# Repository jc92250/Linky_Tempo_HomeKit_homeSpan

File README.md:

# Linky_Tempo_HomeKit

## Introduction

Ceci est la "V2" du projet Linky_Tempo:
L'objectif est de pouvoir accéder au status du délestage ainsi qu'à la possibilité d'annuler ce délestage depuis Internet.

## Le contexte

Le logement est en tout électrique.
Le contrat EDF est en offre Tempo.
En général, hors télétravail, l'appartement est vide dans la journée.
L'environnement informatique est orienté Apple (mac, iPhone, appleTV)

## Rappel du besoin

Le besoin est de délester le chauffage (le basculer en hors-gel) automatiquement:
- en heure pleine jour rouge (HPJR) et jour blanc (HPJW)
- en cas de surconsommation

A la demande, il faut pouvoir annuler le délestage en HPJW (mais pas en HPJR)
Cette annulation du délestage doit pouvoir se faire même si on se trouve hors de la maison.
 
## L'approche suivie

Par rapport au projet Linky_Tempo, l'approche suivie sera de:
- remplacer l'Arduino par un ESP32
- installer HomeSpan sur l'ESP32 pour qu'il soit vu comme un device HomeKit
- le configurer comme un "Thermostat"

Pourquoi "Thermostat" ?  
Car cela semble être le device dont les fonctionnalités sont les plus proches de celles qu'on veut obtenir.  
Voici ses différents modes de fonctionnement (CurrentHeatingCoolingState) et leur usage prévu:
- IDLE: utilisé, délestage possible en fonction des infos du Linky
- HEATING: délestage annulé, chauffage actif
- COOLING: pas utilisé

Concernant la commande (TargetHeatingCoolingState) on a:
- OFF: pas utilisé
- HEAT: annulation du délestage, activer le chauffage (sauf si surconsommation)
- COOL: pas utilisé
- AUTO: mode automatique (délestage HPJR, HPJW et surconsommation)

Le circuit a également un bouton poussoir permettant de basculer entre le mode automatique et le mode annulation du délestage.

Note: "Heater-Cooler" aurait peut-être pu être utilisé à la place de "Thermostat". Mais cette possibilité n'a pas été étudiée.

## Partie électronique
Le mode "Thermostat" de HomeKit permettant d'afficher une température, une sonde BME280 a été rajoutée au projet.
Le circuit a été monté sur une plaque à trous avec bandes cuivrées. Dans KiCad, la couche "bleue" (B\.cu) corresponds à la face cuivrée alors que la couche "rouge" (F\.Cu) corresponds à la face supérieure sur laquelle on a installé quelques jumpers.
La disposition des composants est très aérée afin de limiter les court-circuits.

## Configuration

Factory reset:  
Faire un appui long (> 10 secondes) sur le bouton reset. Au bout de 3 secondes, la led interne va clignoter rapidement, continuer l'appui sur le bouton jusqu'à l'extinction de la led.

A ce moment, le device est configuré comme un point d'accès wifi sur lequel on peut se connecter avec un ordinateur ou un smartphone. Voici les paramètres du point d'accès:
- nom du wifi: JCDELESTAGE
- mot de passe: 123456789

Via ce point d'accès, il est possible de:
- définir le réseau wifi sur lequel le device doit se connecter
- définir le setup-code homeKit du device

Une fois ces informations saisies, le device va redémarrer et se connecter à ce
réseau wifi. Une fois ceci effectué, la led bleue va flasher 2 fois toutes les 3 secondes pour indiquer qu'il n'est pas encore pairé dans Maison.

## Les LEDs

LED rouge:
- toujours allumée, indique que l'ESP32 est alimenté

LED bleue:  
- allumée fixe: le device est en fonctionnement et pairé dans Maison
- allumée et clignotante (2 flashs brefs toutes les 3 secondes): le device n'est pas pairé dans Maison.

LED jaune:
- flashe à chaque fois qu'une trame Linky valide a été reçue
- reste allumée lorsque le délestage est annulé

## Limitation

A l'allumage du circuit, le chauffage est initilisé en mode délestage.
Il n'est pas possible de désactiver ce délestage et commencer à chauffer.
Il faut attendre quelques (4, cf TEMPS_DELESTAGE) minutes.

## Quelques informations techniques

Utiliser Arduino IDE pour builder le code et l'uploader sur l'ESP32

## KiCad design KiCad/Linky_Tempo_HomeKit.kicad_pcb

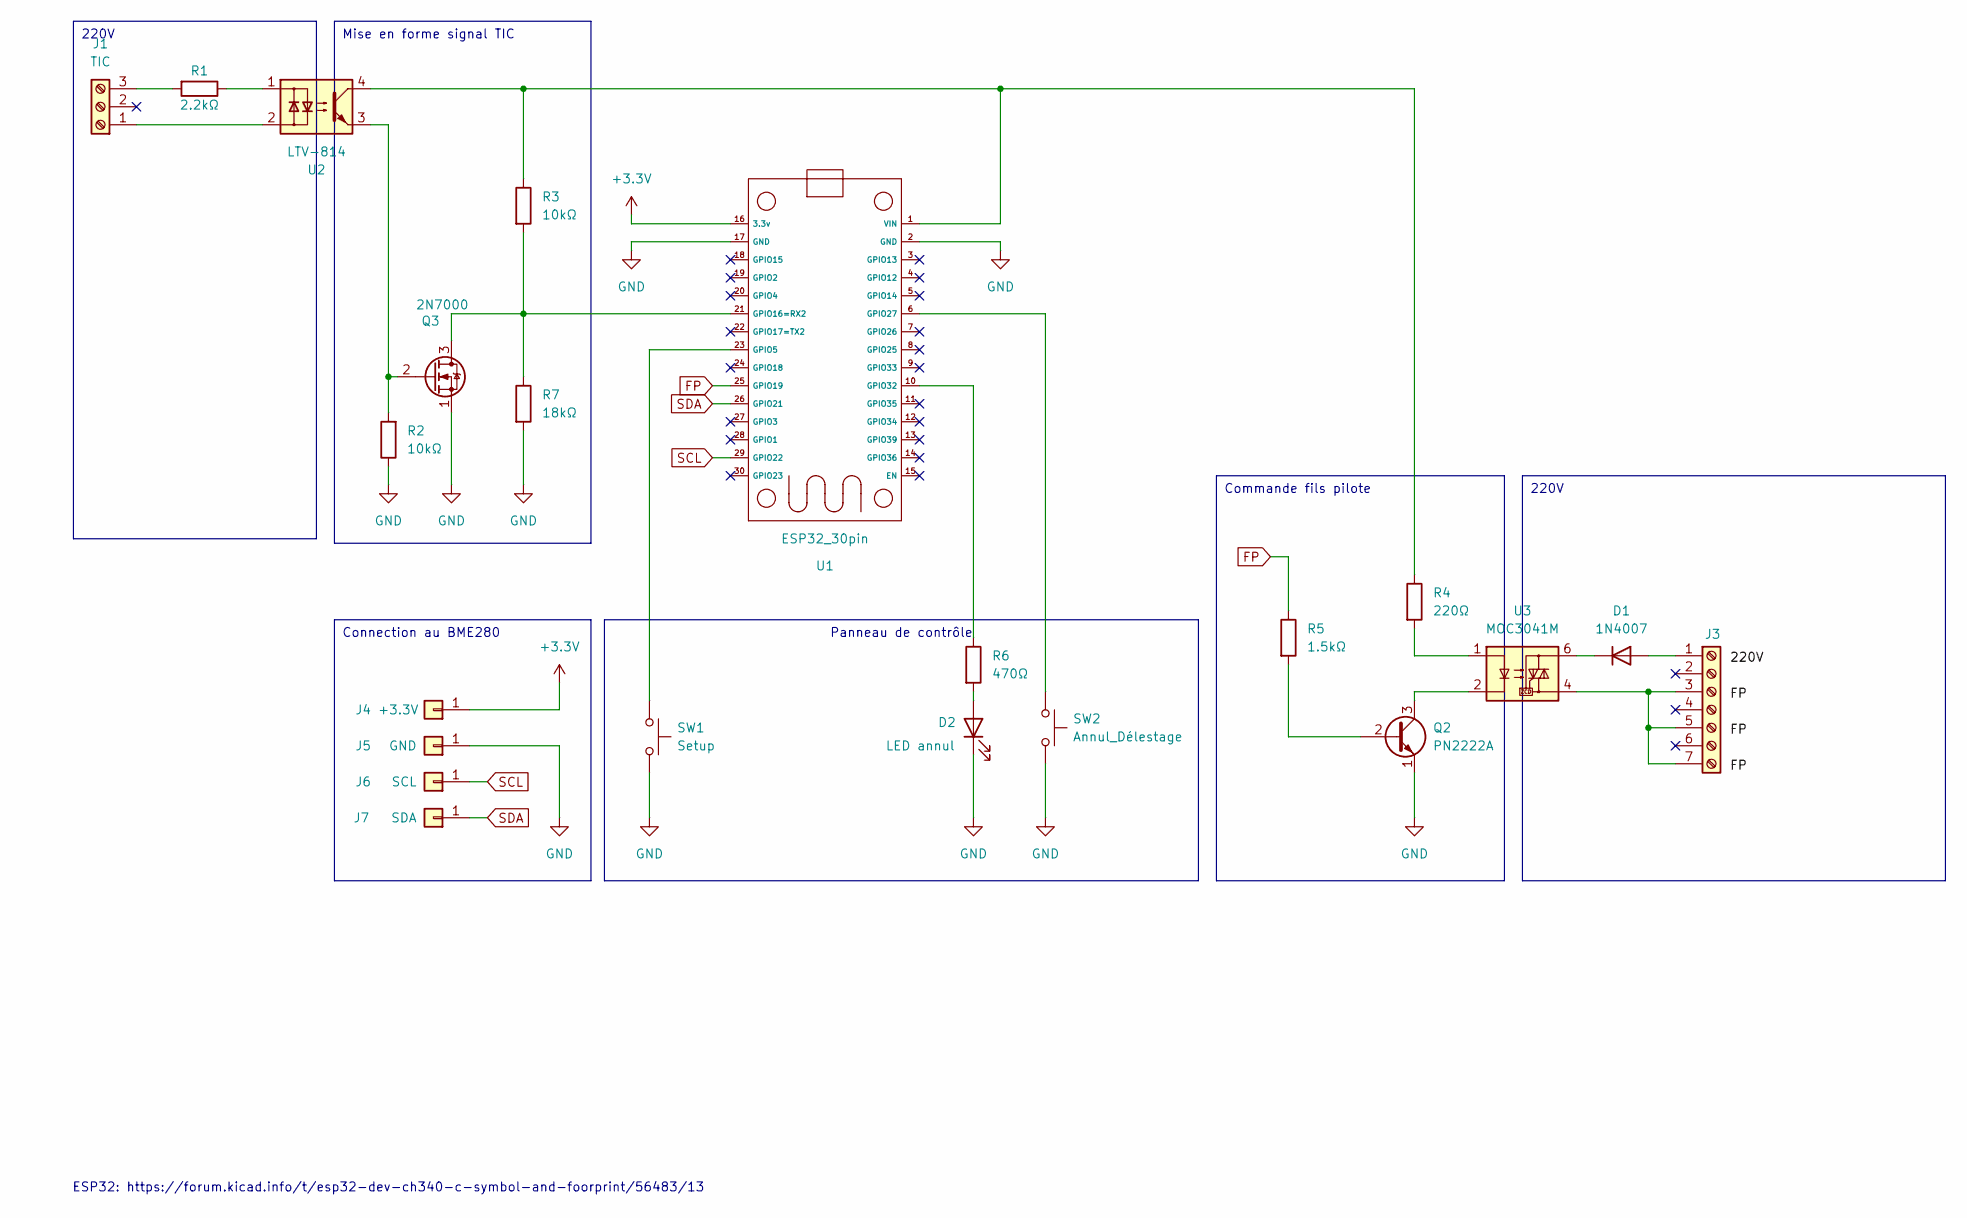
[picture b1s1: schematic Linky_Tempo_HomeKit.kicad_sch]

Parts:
D1: 1N4007; D_DO-15_P15.24mm_Horizontal
D2: LED annul; LED_D3.0mm
J1: TIC; PinSocket_1x03_P2.54mm_Vertical
J3: Main(1) + Fil pilote (3,5,7); PinSocket_1x07_P2.54mm_Vertical
J4: +3.3V; PinHeader_1x01_P2.54mm_Vertical
J5: GND; PinHeader_1x01_P2.54mm_Vertical
J6: SCL; PinHeader_1x01_P2.54mm_Vertical
J7: SDA; PinHeader_1x01_P2.54mm_Vertical
Q2: PN2222A; TO-92_Inline_Wide
Q3: 2N7000; TO-92_Inline
R1: 2.2kΩ; R_Axial_DIN0207_L6.3mm_D2.5mm_P2.54mm_Vertical
R2: 10kΩ; R_Axial_DIN0207_L6.3mm_D2.5mm_P5.08mm_Vertical
R3: 10kΩ; R_Axial_DIN0309_L9.0mm_D3.2mm_P15.24mm_Horizontal
R4: 220Ω; R_Axial_DIN0207_L6.3mm_D2.5mm_P10.16mm_Horizontal
R5: 1.5kΩ; R_Axial_DIN0309_L9.0mm_D3.2mm_P20.32mm_Horizontal
R6: 470Ω; R_Axial_DIN0204_L3.6mm_D1.6mm_P7.62mm_Horizontal
R7: 18kΩ; R_Axial_DIN0207_L6.3mm_D2.5mm_P10.16mm_Horizontal
SW1: Setup; SW_PUSH_5.08mm_H5mm
SW2: Annul_Délestage; SW_PUSH_5.08mm_H5mm
U1: ESP32_30pin
U2: LTV-814; DIP-4_W7.62mm
U3: MOC3041M; DIP-6_W7.62mm

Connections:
+3.3V: J4.1, U1.16 (3.3v)
FP: R5.1, U1.25 (GPIO19)
GND: D2.1 (K), J5.1, Q2.1 (E), Q3.1 (S), R2.1, R7.2, SW1.2, SW2.2, U1.2 (GND), U1.17 (GND)
unnamed: D1.2 (A), J3.1
unnamed: D1.1 (K), U3.6
unnamed: D2.2 (A), R6.2
unnamed: J1.1, U2.2
unnamed: J1.3, R1.2
unnamed: J3.3, J3.5, J3.7, U3.4
unnamed: Q2.2 (B), R5.2
unnamed: Q2.3 (C), U3.2
unnamed: Q3.3 (D), R3.2, R7.1, U1.21 (GPIO16=RX2)
unnamed: Q3.2 (G), R2.2, U2.3
unnamed: R1.1, U2.1
unnamed: R4.2, U3.1
unnamed: SW1.1, U1.23 (GPIO5)
unnamed: SW2.1, U1.6 (GPIO27)
unnamed: R6.1, U1.10 (GPIO32)
unnamed: R3.1, R4.1, U1.1 (VIN), U2.4
SCL: J6.1, U1.29 (GPIO22)
SDA: J7.1, U1.26 (GPIO21)

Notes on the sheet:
Connection au BME280
Commande fils pilote
220V
Panneau de contrôle
Mise en forme signal TIC
ESP32: https://forum.kicad.info/t/esp32-dev-ch340-c-symbol-and-foorprint/56483/13

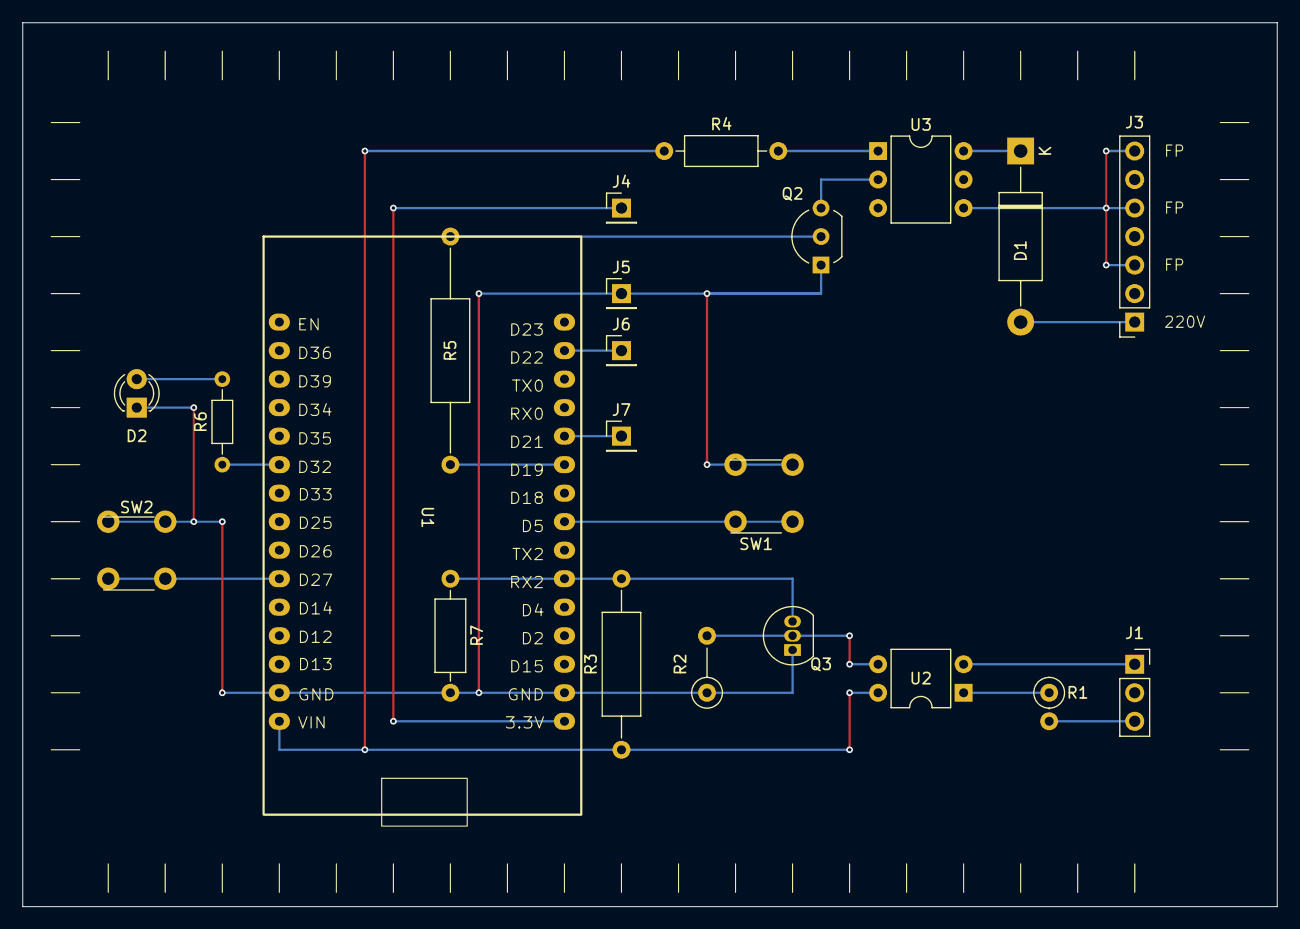
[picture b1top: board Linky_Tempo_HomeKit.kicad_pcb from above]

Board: 2 copper layers, 111.8 x 78.7 mm, 22 parts (0 on the bottom side), 21 nets.

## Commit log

2025-01-26 correction de bugs
2025-01-26 readme et upgrade kicad
2025-11-20 rajouts dans le readme
2025-11-20 typo dans le readme
